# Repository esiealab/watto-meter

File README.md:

# Watto-Meter

## Description

Watto-Meter is an open-source project designed to measure the power consumption of a device connected via USB-C. This project combines dedicated hardware and embedded software to provide the following features:

- **Power measurement**: Voltage, current, and power are measured.
- **Data logging**: Measurements are saved on an SD card in CSV format.
- **Web interface**: Data is accessible via a web page hosted on the device. The interface also allows:
  - Starting or stopping measurements.
  - Downloading or deleting recorded CSV files.
- **Web API**: A REST API enables remote control of the device and access to the data.

## Key Features

1. **Measurement**:
   - Voltage (Volts)
   - Current (mA)
   - Power (Watts)

2. **Data logging**:
   - Measurements are saved on an SD card in CSV format.

3. **User interface**:
   - An intuitive web interface to view data, configure the device, and manage recorded files.

4. **REST API**:
   - Remote control via HTTP endpoints to start/stop measurements, configure the device, or download files.

---

## Open-Source Hardware

The hardware for Watto-Meter is also open-source, created by [@Hyrla](https://github.com/Hyrla). All the files required to manufacture the PCB and assemble the device are available in the [`hardware/`](hardware/) folder.

### Hardware Image

Below is an image of the Watto-Meter hardware:

---

## Software Development and Deployment

### Prerequisites

- [PlatformIO Core](https://docs.platformio.org/page/core.html)
- A Watto-Meter board (see the [`hardware/`](hardware/) folder)
- An SD card for data logging

### Instructions

1. **Clone the project**:
   ```bash
   git clone https://github.com/esiealab/watto-meter.git
   cd watto-meter/software
   ```

2. **Configure the project**:
   - Open the folder in PlatformIO.
   - Edit the [`platformio.ini`](software/platformio.ini) file if necessary and the [`WiFiConfig.h`](software/include/WiFiConfig.h) (WiFi SSID, password.).

3. **Build and upload the firmware**:
   ```bash
   pio run --target upload
   ```

4. **Upload folder [`data`](software/data/) to the filesystem**:
According to [this guide](https://randomnerdtutorials.com/esp32-vs-code-platformio-spiffs/):
   ```bash
   #Build the filesystem image
   pio run --target buildfs
   #Upload the filesystem image
   pio run --target uploadfs
   ```
Or you can open the PlatformIO menu and click on the following buttons:

---

## License

This project is licensed under the MIT License. You are free to use, modify, and distribute it, provided you retain the copyright notice.

---

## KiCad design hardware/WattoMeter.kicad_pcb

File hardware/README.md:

## Open-Source Hardware

The hardware for Watto-Meter is also open-source, created by [@Hyrla](https://github.com/Hyrla). All the files required to manufacture the PCB and assemble the device are available in the [`hardware/`](hardware/) folder.

### Hardware Image

Below is an image of the Watto-Meter hardware:

### Ordering the PCB on JLCPCB

To manufacture the PCB, you can use JLCPCB's fabrication service. Follow these steps:

1. **Download the Gerber files**:
   - The Gerber files required for fabrication are located in the [`hardware/`](hardware/) folder.

2. **Create an account on JLCPCB**:
   - Visit [https://jlcpcb.com](https://jlcpcb.com) and create an account.

3. **Upload the Gerber files**:
   - Click "Quote Now" and upload the Gerber files for the project.

4. **Configure fabrication options**:
   - Select your desired options (PCB color, thickness, etc.).

5. **Order components**:
   - If you want the PCB assembled, upload the Bill of Materials (BOM) and Component Placement List (CPL) files available in the [`hardware/production/`](hardware/production/) folder.

6. **Place the order**:
   - Confirm your order and wait for delivery.

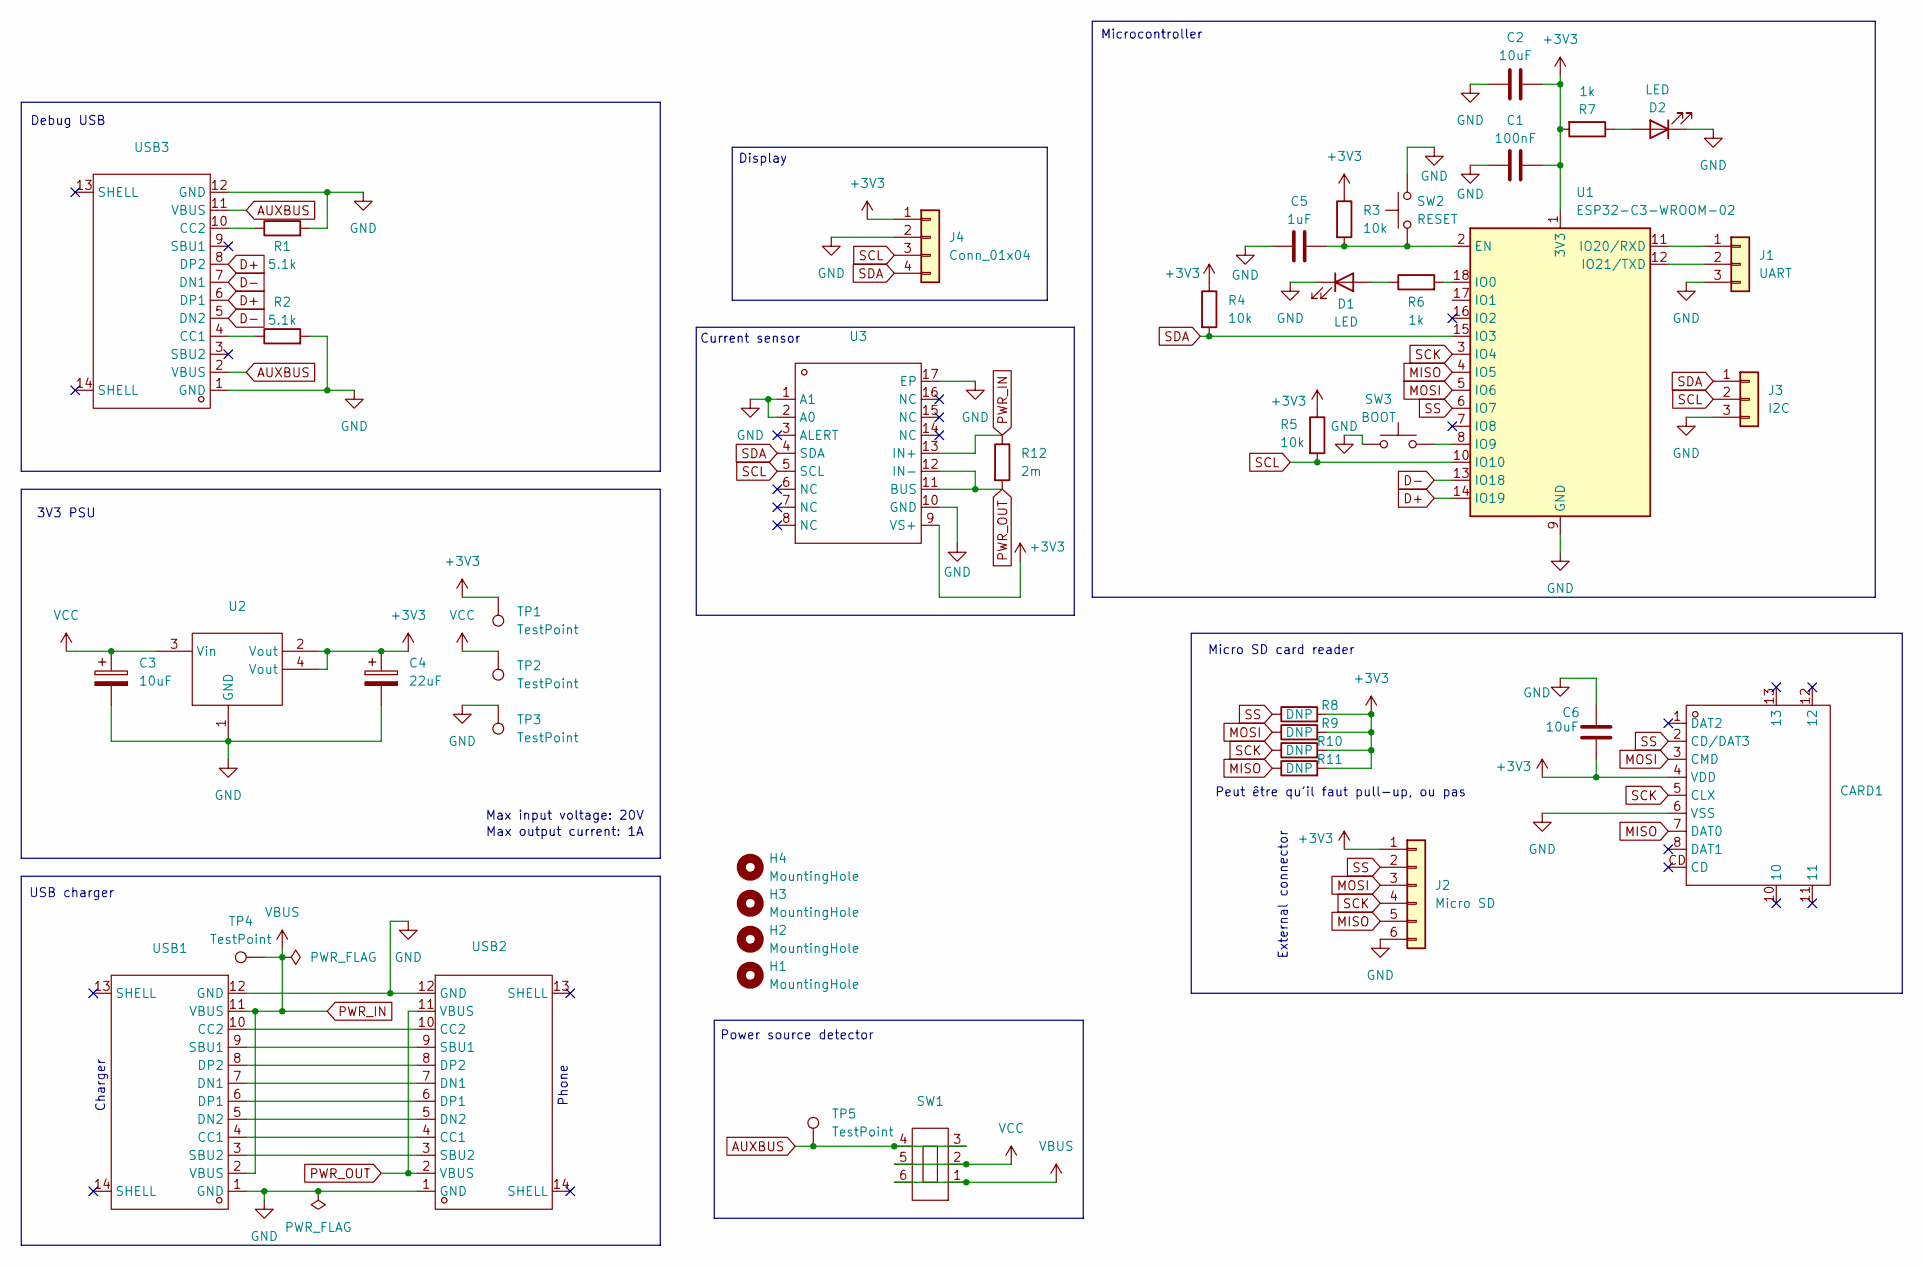
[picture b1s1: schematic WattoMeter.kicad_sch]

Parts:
C1: 100nF; C_0603_1608Metric_Pad1.08x0.95mm_HandSolder
C2, C6: 10uF; C_0603_1608Metric_Pad1.08x0.95mm_HandSolder
C3: 10uF; CP_EIA-3528-21_Kemet-B_Pad1.50x2.35mm_HandSolder
C4: 22uF; CP_EIA-3216-18_Kemet-A_Pad1.58x1.35mm_HandSolder
C5: 1uF; C_0603_1608Metric_Pad1.08x0.95mm_HandSolder
CARD1: TF-SMD_TF-PUSH; Manufacturer Part TF PUSH; LCSC Part Name 自弹式 MicroSD卡(TF卡) 卡座
D1, D2: LED; LED_0603_1608Metric_Pad1.05x0.95mm_HandSolder
H1, H2, H3, H4: MountingHole; MountingHole_3.2mm_M3
J1: UART; PinSocket_1x03_P2.54mm_Vertical_SMD_Pin1Right
J2: Micro SD; PinSocket_1x06_P2.54mm_Vertical_SMD_Pin1Left
J3: I2C; PinSocket_1x03_P2.54mm_Vertical_SMD_Pin1Right
J4: Conn_01x04; PinSocket_1x04_P2.54mm_Vertical_SMD_Pin1Right
R1, R2: 5.1k; R_0603_1608Metric_Pad0.98x0.95mm_HandSolder
R3, R4, R5: 10k; R_0603_1608Metric_Pad0.98x0.95mm_HandSolder
R6, R7: 1k; R_0603_1608Metric_Pad0.98x0.95mm_HandSolder
R8, R9, R10, R11: DNP; R_0603_1608Metric_Pad0.98x0.95mm_HandSolder
R12: 2m; R_2512_6332Metric_Pad1.40x3.35mm_HandSolder
SW1: SW-SMD_HOOYA_MS-22D17AG2.5-B; Manufacturer Part MS-22D17-G2; LCSC Part Name 微型拨动开关
SW2: RESET; SW-SMD_L6.0-W3.3-LS8.0
SW3: BOOT; SW-SMD_L6.0-W3.3-LS8.0
TP1, TP2, TP3, TP4, TP5: TestPoint; TestPoint_Pad_D2.0mm
U1: ESP32-C3-WROOM-02
U2: SOT-223-4_L6.5-W3.5-P2.30-LS7.0-BR; Manufacturer Part CJT1117B-3.3; LCSC Part Name 输入15V 输出3.3V 1A
U3: VQFN-16_L3.0-W3.0-P0.50-TL-EP; Manufacturer Part INA230AIRGTT; LCSC Part Name 高侧或低侧测量双向电流/功率监控器带I2C接口
USB1, USB2, USB3: USB-C-SMD_TYPE-C-6PIN-2MD-073; Manufacturer Part TYPE-C 16PIN 2MD(073); LCSC Part Name Type-C 母 卧贴

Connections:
+3V3: C1.1, C2.1, C4.1, C6.2, CARD1.4 (VDD), J2.1, J4.1, R3.1, R4.1, R5.1, R7.2, R8.2, R9.2, R10.2, R11.2, TP1.1, U1.1 (3V3), U2.2 (Vout), U2.4 (Vout), U3.9 (VS+)
AUXBUS: SW1.3, SW1.4, TP5.1, USB3.2 (VBUS), USB3.11 (VBUS)
D+: U1.14 (IO19), USB3.6 (DP1), USB3.8 (DP2)
D-: U1.13 (IO18), USB3.5 (DN2), USB3.7 (DN1)
GND: C1.2, C2.2, C3.2, C4.2, C5.2, C6.1, CARD1.6 (VSS), D1.1 (K), D2.1 (K), J1.3, J2.6, J3.3, J4.2, R1.2, R2.2, SW2.2, SW3.1, TP3.1, U1.9 (GND), U1.19 (GND), U2.1 (GND), U3.1 (A1), U3.2 (A0), U3.10 (GND), U3.17 (EP), USB1.1 (GND), USB1.12 (GND), USB2.1 (GND), USB2.12 (GND), USB3.1 (GND), USB3.12 (GND)
MISO: CARD1.7 (DAT0), J2.5, R11.1, U1.4 (IO5)
MOSI: CARD1.3 (CMD), J2.3, R9.1, U1.5 (IO6)
unnamed: D1.2 (A), R6.1
unnamed: D2.2 (A), R7.1
unnamed: J1.1, U1.11 (IO20/RXD)
unnamed: J1.2, U1.12 (IO21/TXD)
unnamed: C5.1, R3.2, SW2.1, U1.2 (EN)
unnamed: R6.2, U1.18 (IO0)
unnamed: SW3.2, U1.8 (IO9)
unnamed: USB1.4 (CC1), USB2.4 (CC1)
unnamed: USB1.10 (CC2), USB2.10 (CC2)
unnamed: USB1.7 (DN1), USB2.7 (DN1)
unnamed: USB1.5 (DN2), USB2.5 (DN2)
unnamed: USB1.6 (DP1), USB2.6 (DP1)
unnamed: USB1.8 (DP2), USB2.8 (DP2)
unnamed: USB1.9 (SBU1), USB2.9 (SBU1)
unnamed: USB1.3 (SBU2), USB2.3 (SBU2)
unnamed: R2.1, USB3.4 (CC1)
unnamed: R1.1, USB3.10 (CC2)
PWR_IN: R12.1, SW1.1, SW1.6, TP4.1, U3.13 (IN+), USB1.2 (VBUS), USB1.11 (VBUS)
PWR_OUT: R12.2, U3.11 (BUS), U3.12 (IN-), USB2.2 (VBUS), USB2.11 (VBUS)
SCK: CARD1.5 (CLX), J2.4, R10.1, U1.3 (IO4)
SCL: J3.2, J4.3, R5.2, U1.10 (IO10), U3.5 (SCL)
SDA: J3.1, J4.4, R4.2, U1.15 (IO3), U3.4 (SDA)
SS: CARD1.2 (CD/DAT3), J2.2, R8.1, U1.6 (IO7)
VCC: C3.1, SW1.2, SW1.5, TP2.1, U2.3 (Vin)

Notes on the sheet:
Max input voltage: 20V
Current sensor
Micro SD card reader
3V3 PSU
Display
Power source detector
Microcontroller
External connector
USB charger
Phone
Peut être qu'il faut pull-up, ou pas
Debug USB
Charger
Max output current: 1A

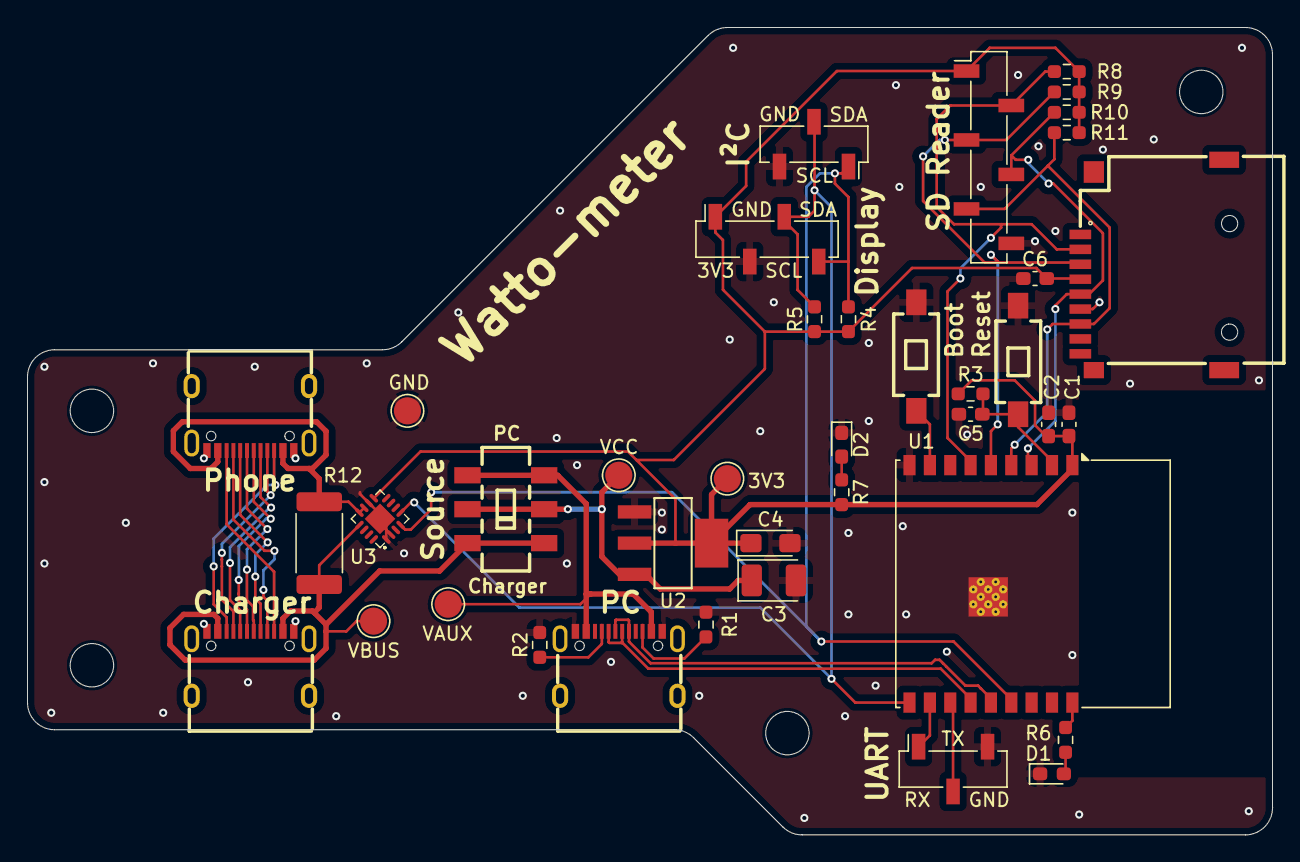
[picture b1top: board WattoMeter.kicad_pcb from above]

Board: 2 copper layers, 91.8 x 59.5 mm, 43 parts (0 on the bottom side), 31 nets.

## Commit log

2025-04-28 First version, created by @Hyrla
2025-04-29 Migrate to PlatformIO, merge example with INA, Screen, SD, Wifi, NTP.
2025-04-30 Add WifiManager
2025-04-30 Exclude WiFiConfig.h
2025-05-06 Add first version of the API and Web Interface
2025-05-07 Correct Watto-Meter title
2025-05-07 Add Watto-Meter zip file for PCB production
2025-05-07 First version of READMEs
2025-05-07 Center images in README... yes, it's important.
2025-05-07 Update links
2025-05-07 Correct last links
2025-05-07 Add "device" parameter to /startMeasures and add endpoint to list files in JSON
2025-05-07 Creates RT Tasks for display and measures
2025-05-12 Refactor WiFiController to remove ssid and password from constructor; update connection method to accept parameters
2025-05-14 Refactor DisplayManager and WiFiController: update display methods and remove WiFiConfig; enhance WiFi connection handling
2025-05-14 Remove SDManager and related functionality; integrate SD card handling directly in main application logic. Separate I2C reading and SD writing to increase the maximum frequency of reading.
2025-05-15 Update formatCurrentTime method to include milliseconds parameter; adjust related time formatting logic in WiFiController and main application
2025-05-15 - Refactor measurement data structure: add powerWatts field and update related CSV logging in writeSDTask - Change INA parameter to request new conversion each microsecond and a value after 128 conve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
2025-05-16 - Refactor WiFiController: update time handling methods to use microseconds and adjust related logic in main application - Correct error using a global measurement variable
2025-05-16 Add example to read and display data
2025-05-16 Add checks to test if everything is OK in the dataframe
